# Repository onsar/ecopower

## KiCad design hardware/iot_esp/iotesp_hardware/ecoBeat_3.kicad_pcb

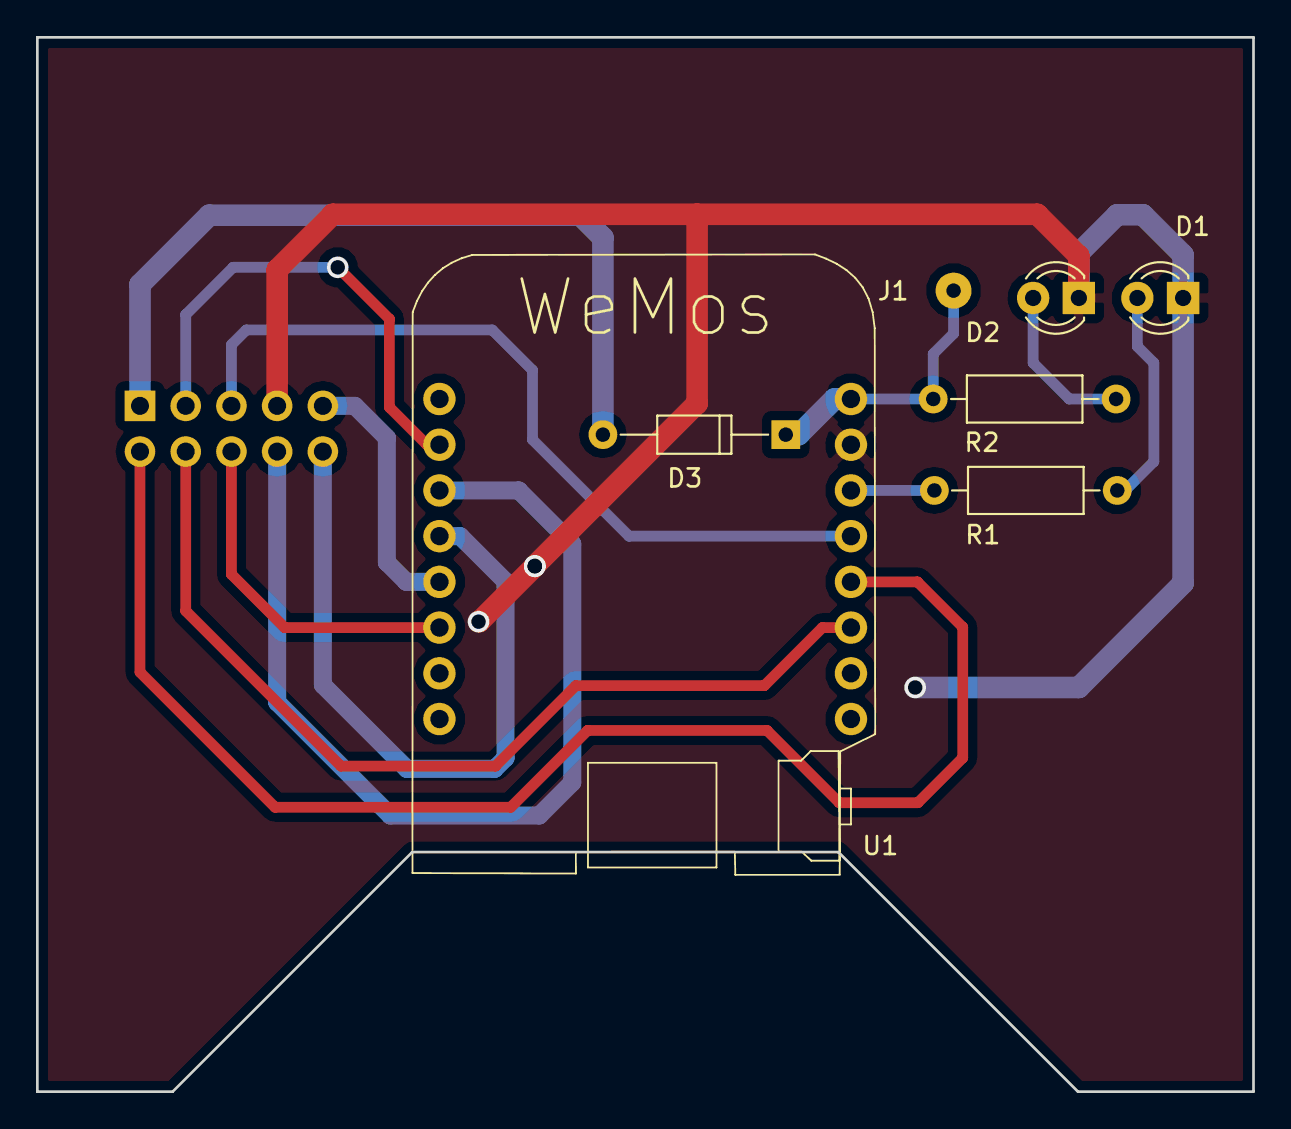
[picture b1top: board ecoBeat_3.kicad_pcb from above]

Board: 2 copper layers, 67.6 x 58.6 mm, 8 parts (1 on the bottom side), 14 nets.

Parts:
D1, D2: LED; LED_D3.0mm
D3: Schottky; D_DO-35_SOD27_P10.16mm_Horizontal
J1: Test; SolderWirePad_single_0-8mmDrill
P1: CONN_02X05; Pin_Header_Straight_2x05_Pitch2.54mm_onsar
R1, R2: 220; R_Axial_DIN0207_L6.3mm_D2.5mm_P10.16mm_Horizontal
U1: WeMos_mini; D1_mini_board

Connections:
/esp_d0: P1.6, U1.3
/esp_d1: P1.4, U1.14
/esp_d2: P1.2, U1.13
/esp_d3: P1.5, U1.12
/esp_d4: R1.2, U1.11
/esp_d8: P1.3, U1.7
/miso: P1.10, U1.5
/mosi: P1.8, U1.6
/sck: P1.9, U1.4
/vcc_5v: D3.2, P1.1
/vin_5v: D3.1, J1.1, R2.2, U1.9
GND: D1.1, D2.1, P1.7, U1.10
unnamed: D1.2, R1.1
unnamed: D2.2, R2.1

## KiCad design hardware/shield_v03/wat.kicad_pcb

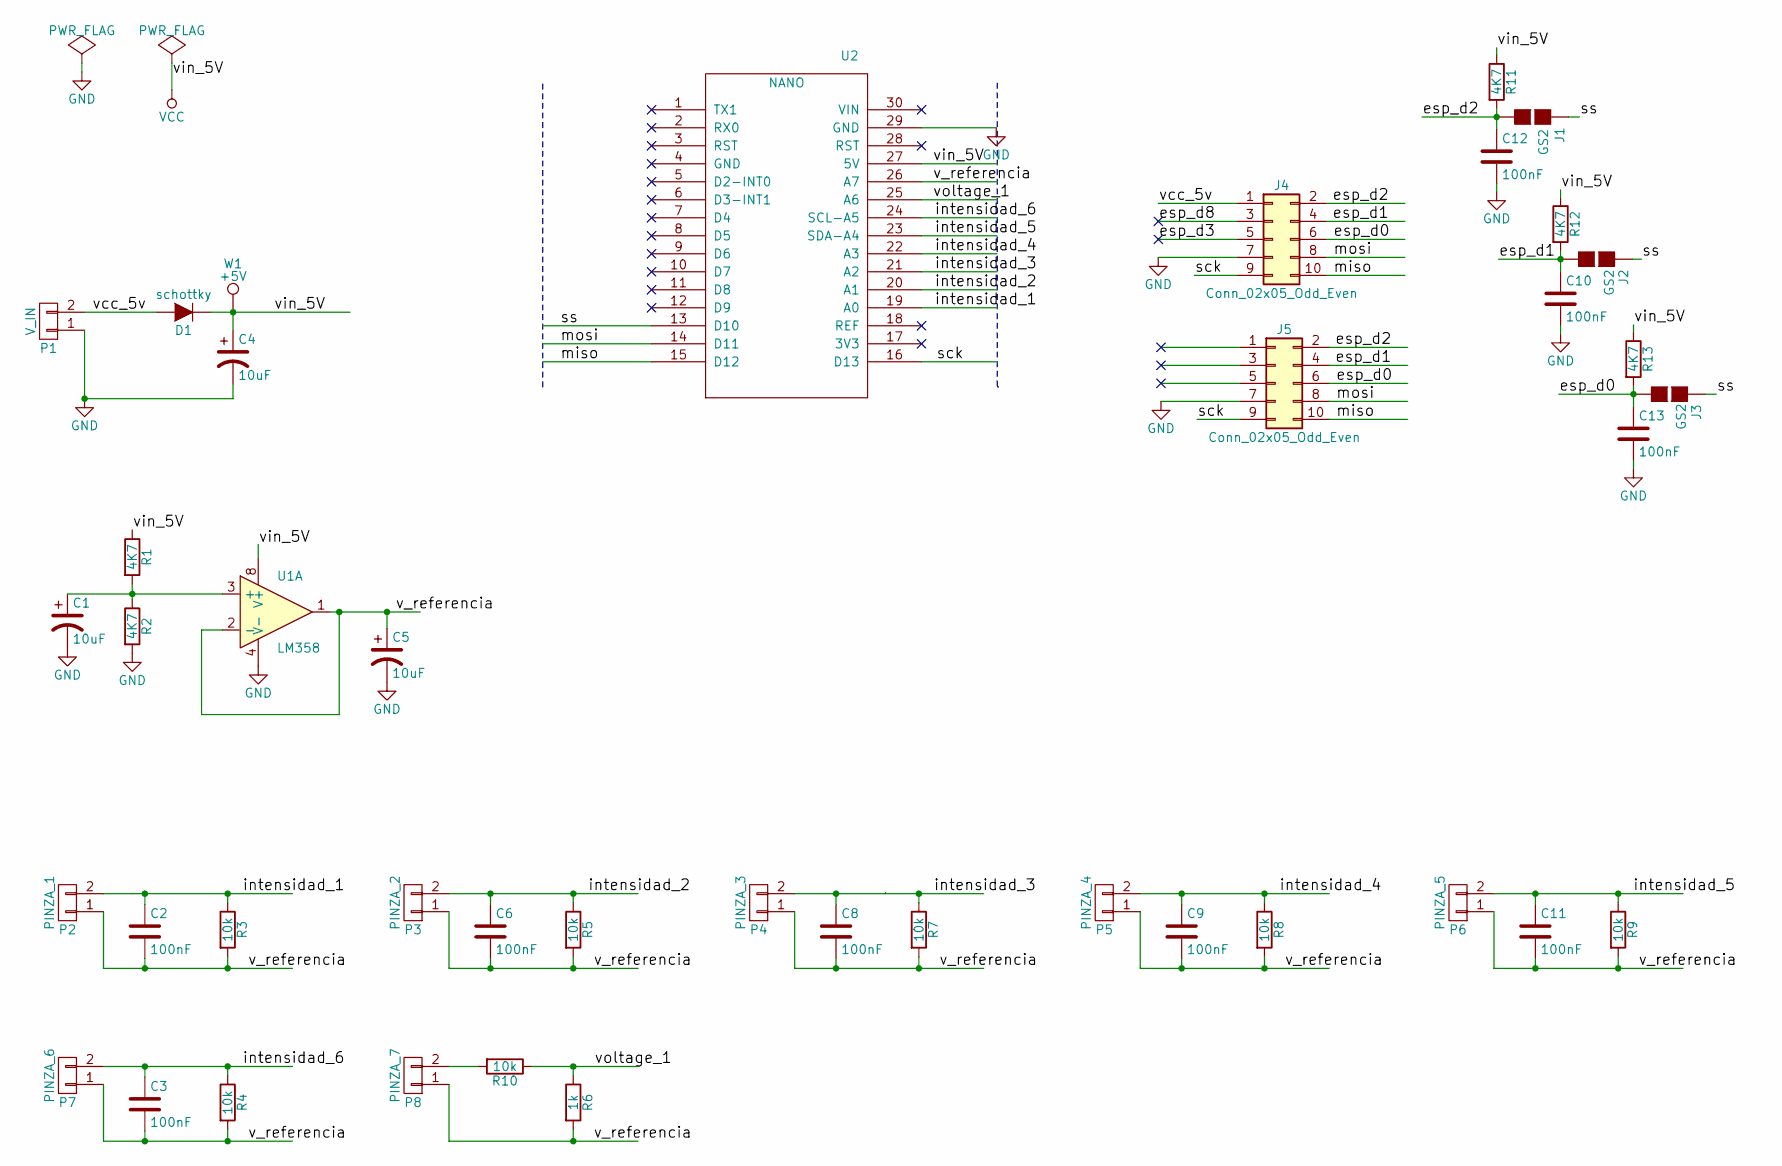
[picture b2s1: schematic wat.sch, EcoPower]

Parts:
C1, C4, C5: 10uF; C_2220_HandSoldering
C2, C3, C6, C8, C9, C10, C11, C12, C13: 100nF; C_1206_HandSoldering
D1: schottky; D_2114
J1, J2, J3: GS2
J4, J5: Conn_02x05_Odd_Even; Pin_Header_Straight_2x05_Pitch2.54mm_onsar
P1: V_IN; TerminalBlock_bornier-2_P5.08mm
P2: PINZA_1; TerminalBlock_bornier-2_P5.08mm
P3: PINZA_2; TerminalBlock_bornier-2_P5.08mm
P4: PINZA_3; TerminalBlock_bornier-2_P5.08mm
P5: PINZA_4; TerminalBlock_bornier-2_P5.08mm
P6: PINZA_5; TerminalBlock_bornier-2_P5.08mm
P7: PINZA_6; TerminalBlock_bornier-2_P5.08mm
P8: PINZA_7; TerminalBlock_bornier-2_P5.08mm
R1, R2, R11, R12, R13: 4K7; R_1206_HandSoldering
R3, R4, R5, R7, R8, R9: 10k; Resistor_Horizontal_RM10mm
R6: 1k; Resistor_Horizontal_RM10mm
R10: 10k; R_1206_HandSoldering
U1: LM358; SO-8_5.3x6.2mm_Pitch1.27mm
U2: NANO; arduino_nano
W1: +5V; SolderWirePad_single_0-8mmDrill

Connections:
/esp_d0: C13.1, J3.2 (G2), J4.6, J5.6, R13.2
/esp_d1: C10.1, J2.2 (G2), J4.4, J5.4, R12.2
/esp_d2: C12.1, J1.2 (G2), J4.2, J5.2, R11.2
/esp_d3: J4.5
/esp_d8: J4.3
/intensidad_1: C2.1, P2.2, R3.1, U2.19 (A0)
/intensidad_2: C6.1, P3.2, R5.1, U2.20 (A1)
/intensidad_3: C8.1, P4.2, R7.1, U2.21 (A2)
/intensidad_4: C9.1, P5.2, R8.1, U2.22 (A3)
/intensidad_5: C11.1, P6.2, R9.1, U2.23 (SDA-A4)
/intensidad_6: C3.1, P7.2, R4.1, U2.24 (SCL-A5)
/miso: J4.10, J5.10, U2.15 (D12)
/mosi: J4.8, J5.8, U2.14 (D11)
/sck: J4.9, J5.9, U2.16 (D13)
/ss: J1.1 (G1), J2.1 (G1), J3.1 (G1), U2.13 (D10)
/v_25: C1.1, R1.2, R2.1, U1.3 (+), U1.5 (+)
/v_referencia: C2.2, C3.2, C5.1, C6.2, C8.2, C9.2, C11.2, P2.1, P3.1, P4.1, P5.1, P6.1, P7.1, P8.1, R3.2, R4.2, R5.2, R6.2, R7.2, R8.2, R9.2, U1.1, U1.2 (-), U2.26 (A7)
/vcc_5v: D1.2 (A), J4.1, P1.2
/voltage_1: R6.1, R10.1, U2.25 (A6)
GND: C1.2, C4.2, C5.2, C10.2, C12.2, C13.2, J4.7, J5.7, P1.1, R2.2, U1.4 (V-), U2.29 (GND)
unnamed: P8.2, R10.2
unnamed: U1.6 (-), U1.7
VCC: C4.1, D1.1 (K), R1.1, R11.1, R12.1, R13.1, U1.8 (V+), U2.27 (5V), W1.1

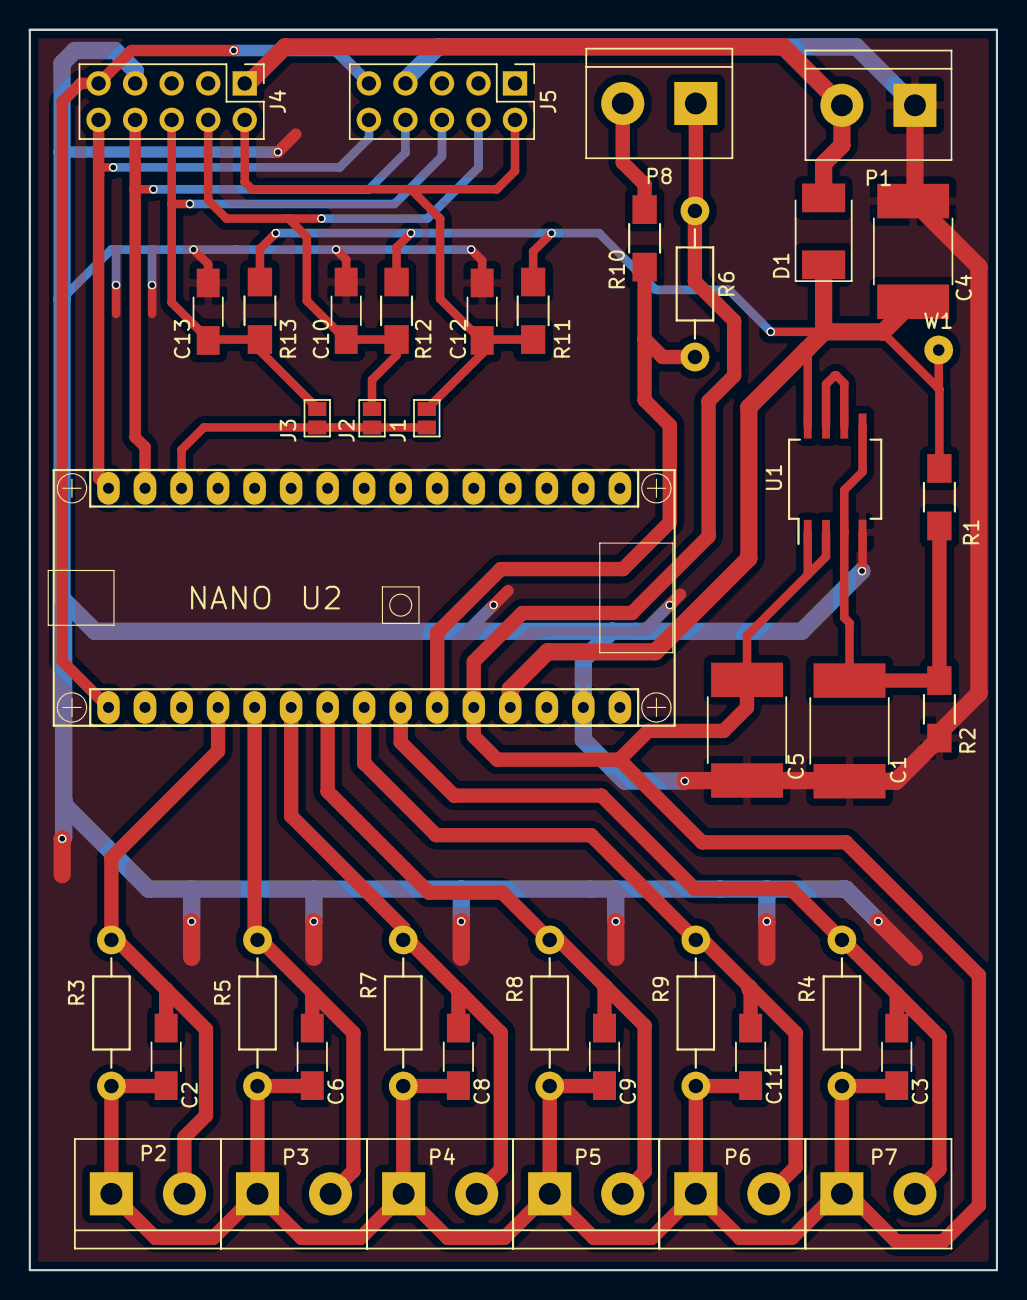
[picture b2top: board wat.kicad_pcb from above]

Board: 2 copper layers, 67.2 x 86.2 mm, 42 parts (0 on the bottom side), 21 nets.

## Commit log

2019-08-10 version de backup, no se ha probado
2019-08-11 sincronizacion varios registros
2019-08-13 transmision robusta con inicio y final de traa
2019-08-15 dos slaves y comprabar tx(55)
2019-08-22 4 esclavos, comprobacion final de trama con suma
2019-08-30 desarrollo hardware
2019-09-02 avance en pcb
2019-09-03 hardware, rehubicacion de componentes
2019-09-08 primera version hardware esclavo
2019-09-11 primera version del esclavo terminada
2019-09-11 inicio desarrollo hardware master
2019-09-12 cambio iot_esp a esp12 por que no hay espacio
2019-09-18 avances en hardware de master
2019-09-18 desarrollo pcb master
2019-09-23 primera versión de hw terminada
2019-10-14 primeras pruebas
2019-10-27 spi con dos exclavos porbado
2019-11-14 añadir a7 en la libreria como tension de referencia
2019-12-04 activar comunicación serie
2019-12-10 PCB iot_esp12 v2 enviada a fabricar
2019-12-16 entrada de voltage
2020-01-13 condicion para v=230
